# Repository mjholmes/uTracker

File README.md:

# uTracker - a micro RF tracker for HAB use

This tracker builds on the basic tracker i built about a year ago. It is based on an Arduino 328 and uses a bespoke PCB with surface mount components to achiever a much smaller form factor than the previous basic tracker.

The board makes use of a dc/dc step up converter providing 3.3v from a single AA/AAA battery. Unusually for smaller boards this uses the NTX2 / NTX2b for the RF transmitter.

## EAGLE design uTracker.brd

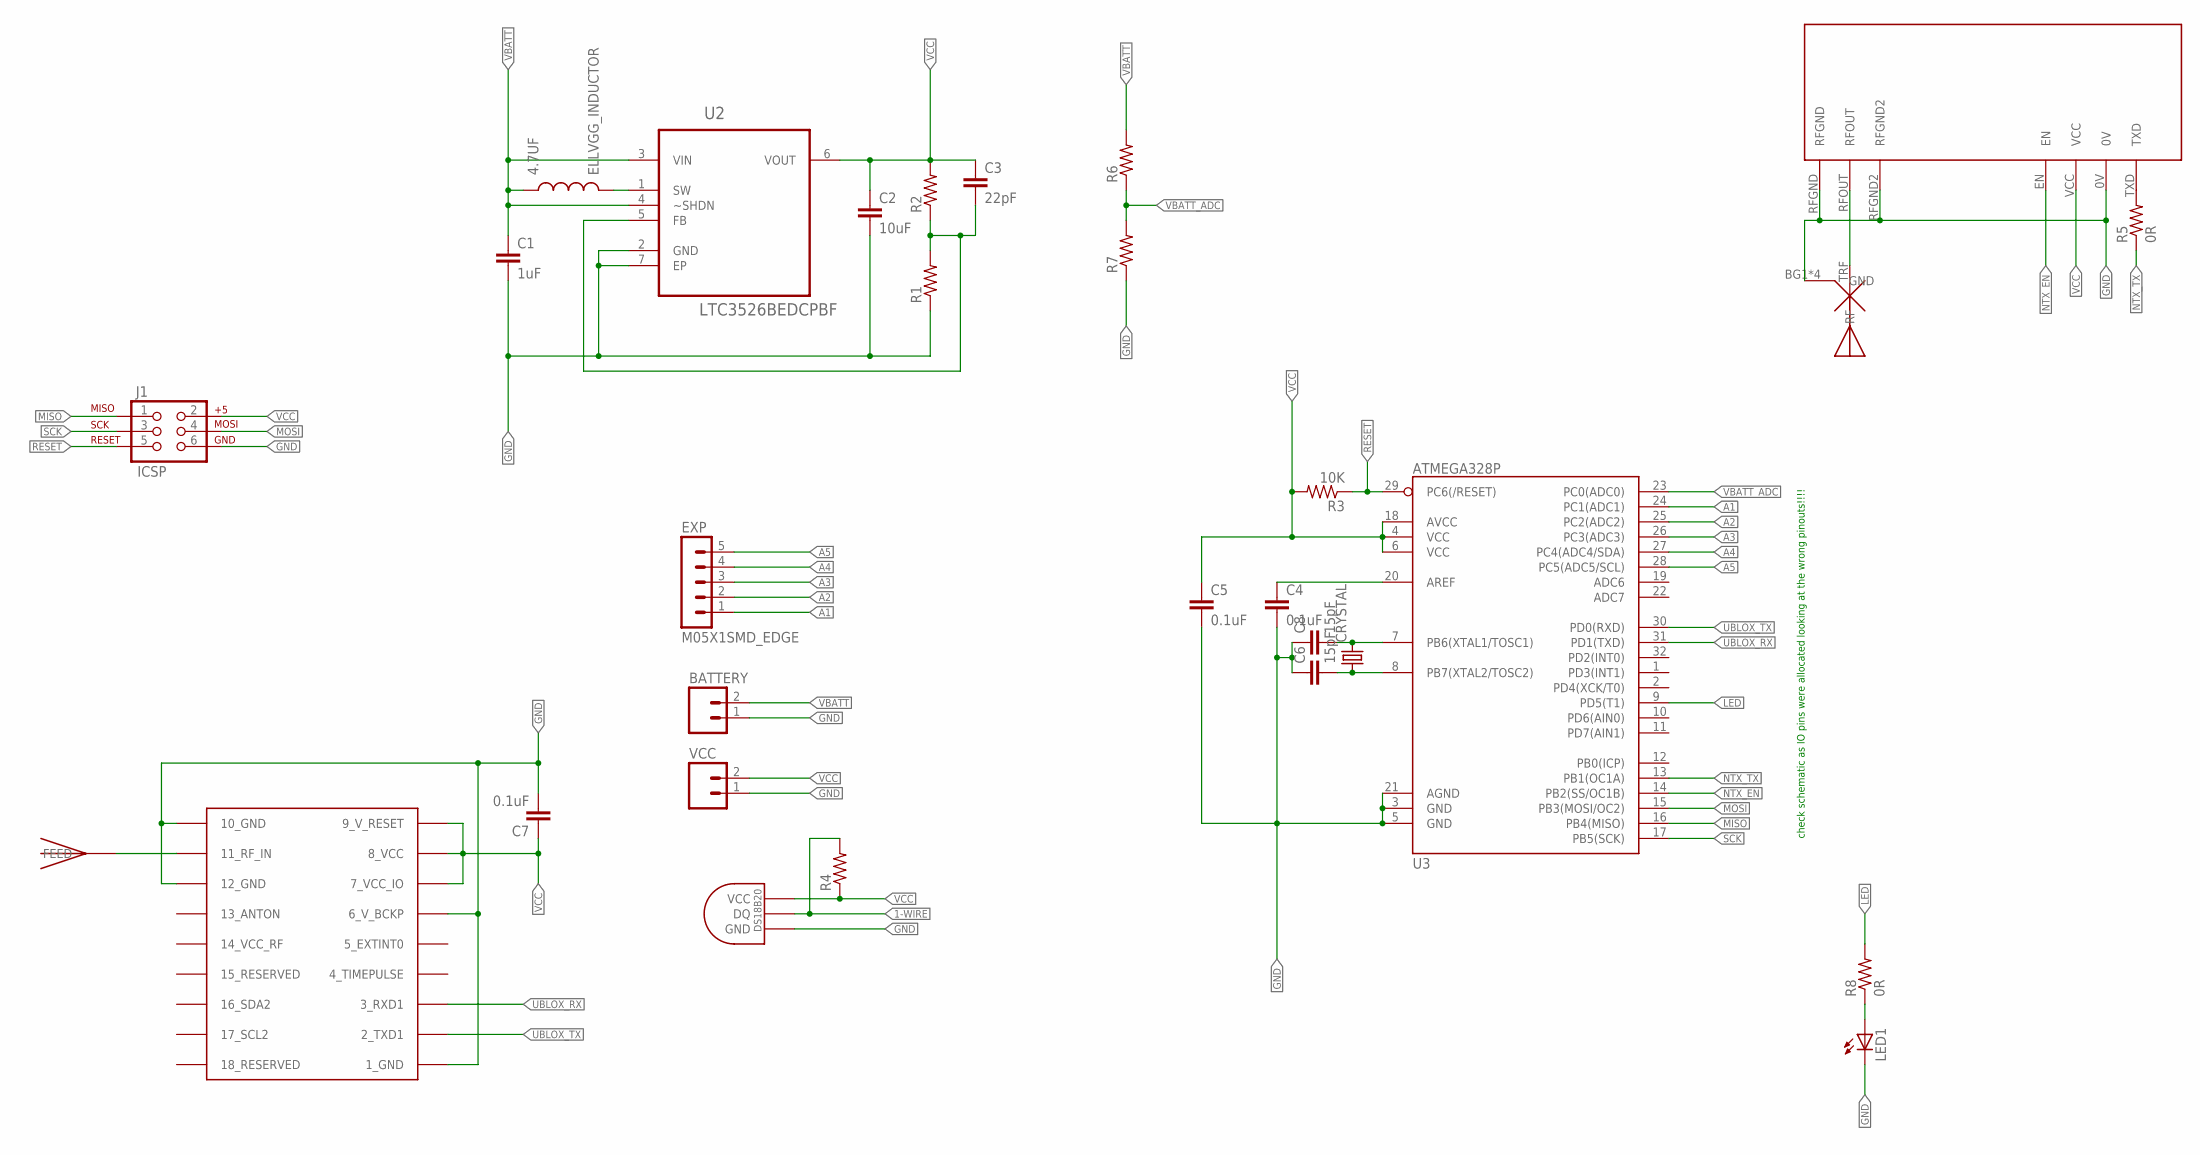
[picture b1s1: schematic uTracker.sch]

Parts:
4.7UF: ELLVGG_INDUCTOR
BATTERY: M02PTH; 1X02
C1: 1uF; 0805
C2: 10uF; 0805
C3: 22pF; 0805
C4, C5, C7: 0.1uF; 0805
C6, C8: 15pF; 0805
CRYSTAL: ABRACON_ABM3_CRYSTALABM03_HC49; ABM03_HC49
EXP: M05X1SMD_EDGE; M05_SMD_EDGE
J1: ICSP; ICSP_SMD_EDGE
LED1: LED1206; LED-1206
R1, R2, R4, R6, R7: RESISTOR0805-RES; 0805
R3: 10K; 0805
R5, R8: 0R; 0805
U2: LTC3526BEDCPBF; DFN200X200X80-7N
U3: ATMEGA328P; TQFP32-08
U$1: ANTENNA; ANTCONN_GNDPL
U$2: JTI_ANTENNA-1575AT43A40
U$3: NTX2
U$4: DS1820SOIC; DS18B20_SOIC
UBLOX: UBLOX_MAX-6
VCC: M02PTH; 1X02

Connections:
1-WIRE: R4.2, U$4.DQ
A1: EXP.1, U3.24 (PC1(ADC1))
A2: EXP.2, U3.25 (PC2(ADC2))
A3: EXP.3, U3.26 (PC3(ADC3))
A4: EXP.4, U3.27 (PC4(ADC4/SDA))
A5: EXP.5, U3.28 (PC5(ADC5/SCL))
GND: BATTERY.1, C1.2, C2.2, C4.2, C5.2, C6.1, C7.2, C8.1, J1.6, LED1.C, R1.1, R7.1, U2.2 (GND), U2.7 (EP), U3.3 (GND), U3.5 (GND), U3.21 (AGND), U$1.BG1 (GND), U$1.BG2 (GND), U$1.TG1 (GND), U$1.TG2 (GND), U$3.0V, U$3.RFGND, U$3.RFGND2, U$4.GND, UBLOX.1_GND, UBLOX.6_V_BCKP, UBLOX.10_GND, UBLOX.12_GND, VCC.1
LED: R8.2, U3.9 (PD5(T1))
MISO: J1.1, U3.16 (PB4(MISO))
MOSI: J1.4, U3.15 (PB3(MOSI/OC2))
unnamed: C3.2, R1.2, R2.1, U2.5 (FB)
unnamed: U$2.FEED, UBLOX.11_RF_IN
unnamed: 4.7UF.P$2 (2), U2.1 (SW)
unnamed: C4.1, U3.20 (AREF)
unnamed: R5.2, U$3.TXD
unnamed: C8.2, CRYSTAL.2, U3.7 (PB6(XTAL1/TOSC1))
unnamed: C6.2, CRYSTAL.1, U3.8 (PB7(XTAL2/TOSC2))
unnamed: U$1.TRF (RF), U$3.RFOUT
unnamed: LED1.A, R8.1
NTX_EN: U3.14 (PB2(SS/OC1B)), U$3.EN
NTX_TX: R5.1, U3.13 (PB1(OC1A))
RESET: J1.5, R3.1, U3.29 (PC6(/RESET))
SCK: J1.3, U3.17 (PB5(SCK))
UBLOX_RX: U3.31 (PD1(TXD)), UBLOX.3_RXD1
UBLOX_TX: U3.30 (PD0(RXD)), UBLOX.2_TXD1
VBATT: 4.7UF.P$1 (1), BATTERY.2, C1.1, R6.2, U2.3 (VIN), U2.4 (~SHDN)
VBATT_ADC: R6.1, R7.2, U3.23 (PC0(ADC0))
VCC: C2.1, C3.1, C5.1, C7.1, J1.2, R2.2, R3.2, R4.1, U2.6 (VOUT), U3.4 (VCC), U3.6 (VCC), U3.18 (AVCC), U$3.VCC, U$4.VCC, UBLOX.7_VCC_IO, UBLOX.8_VCC, UBLOX.9_V_RESET, VCC.2

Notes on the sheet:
check schematic as IO pins were allocated looking at the wrong pinouts!!!!

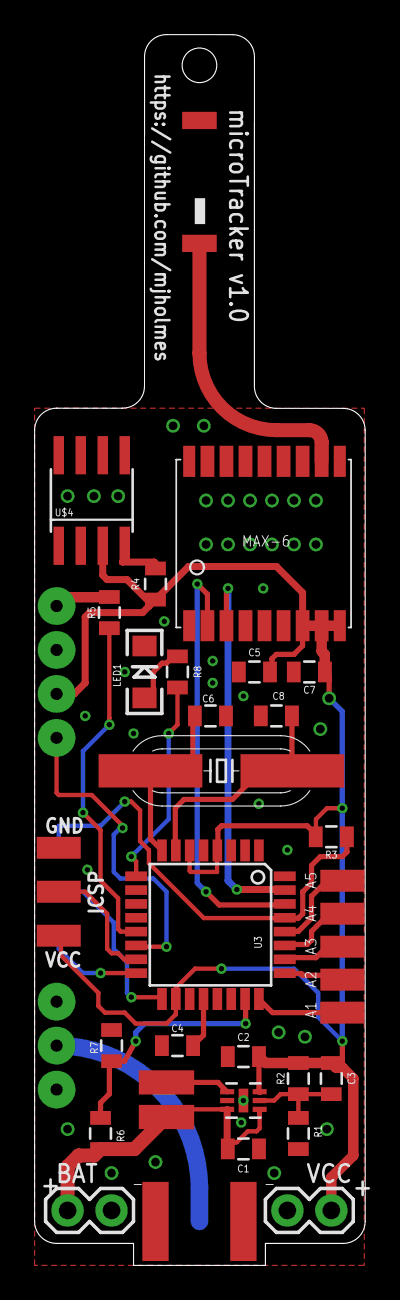
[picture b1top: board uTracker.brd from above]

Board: 2 copper layers, 19.1 x 71.1 mm, 30 parts (1 on the bottom side), 28 nets.

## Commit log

2014-01-09 Final for v1.0
2014-01-09 Modified ICSP header to match 0.1" spacing
    This should ease programming by allowing a standard 2x3 0.1" header to
    be clipped on the side of the board.

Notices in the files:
parts and their libraries:
SparkFun-Capacitors: Licensing: CC v3.0 Share-Alike You are welcome to use this library for commercial purposes.
